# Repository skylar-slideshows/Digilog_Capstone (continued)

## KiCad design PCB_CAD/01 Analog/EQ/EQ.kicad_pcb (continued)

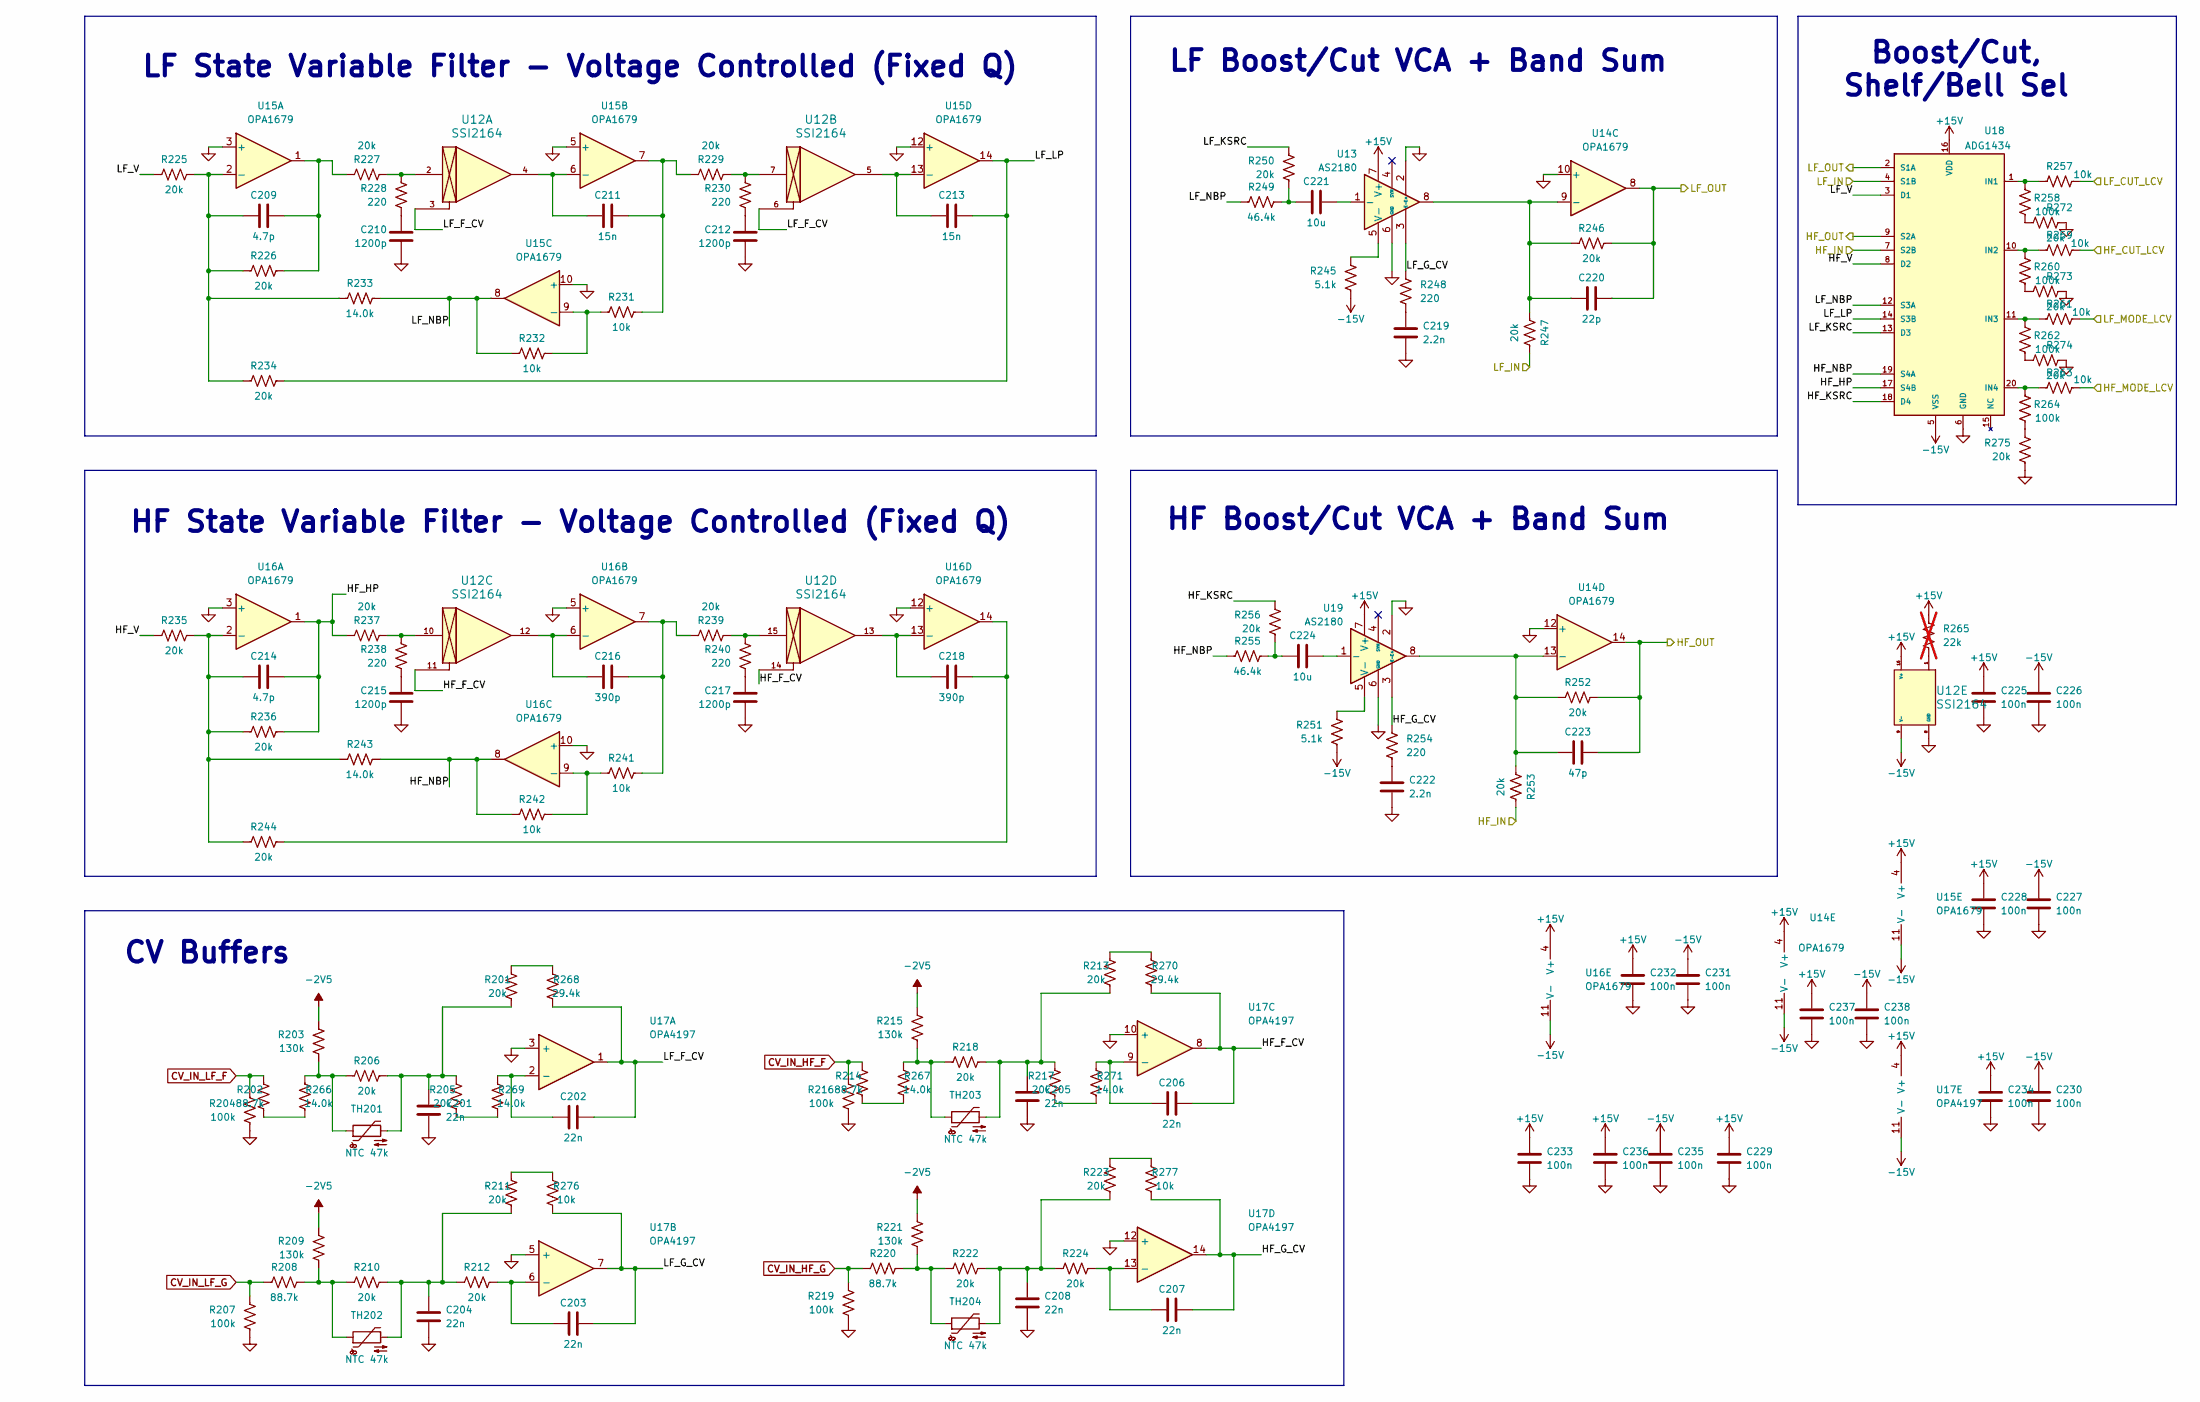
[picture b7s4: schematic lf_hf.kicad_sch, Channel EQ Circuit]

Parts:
C201, C202, C203, C204, C205, C206, C207, C208: 22n; C_1206_3216Metric; LCSC C7500389
C209, C214: 4.7p; C_0603_1608Metric; LCSC C282071
C210, C212, C215, C217: 1200p; C_1206_3216Metric; LCSC C527278
C211, C213: 15n; C_Rect_L7.2mm_W2.5mm_P5.00mm; LCSC dnp
C216, C218: 390p; C_0603_1608Metric; LCSC C107050
C219, C222: 2.2n; C_0805_2012Metric; LCSC C107103
C220: 22p; C_0603_1608Metric; LCSC C105620
C221, C224: 10u; CP_Elec_6.3x5.4_Nichicon; LCSC C340735
C223: 47p; C_0603_1608Metric; LCSC C105622
C225, C226, C227, C228, C229, C230, C231, C232, C233, C234, C235, C236, C237, C238: 100n; C_0603_1608Metric; LCSC C1591
R201, R205, R206, R210, R211, R212, R213, R217, R218, R222, R223, R224, R225, R226, R227, R229, R234, R235, R236, R237, R239, R244, R246, R247, R250, R252, R253, R256, R272, R273, R274, R275: 20k; R_0603_1608Metric; LCSC C311888
R202, R208, R214, R220: 88.7k; R_0603_1608Metric; LCSC C728599
R203, R209, R215, R221: 130k; R_0603_1608Metric; LCSC C473257
R204, R207, R216, R219, R258, R260, R262, R264: 100k; R_0603_1608Metric; LCSC C122538
R228, R230, R238, R240, R248, R254: 220; R_0603_1608Metric; LCSC C318124
R231, R232, R241, R242, R257, R259, R261, R263, R276, R277: 10k; R_0603_1608Metric; LCSC C95204
R233, R243, R266, R267, R269, R271: 14.0k; R_0603_1608Metric; LCSC C705941
R245, R251: 5.1k; R_0603_1608Metric; LCSC C122969
R249, R255: 46.4k; R_0603_1608Metric; LCSC C861420
R265: 22k; R_0603_1608Metric; LCSC C335085; not fitted
R268, R270: 29.4k; R_0603_1608Metric; LCSC C667085
TH201, TH202, TH203, TH204: NTC 47k; R_Axial_DIN0207_L6.3mm_D2.5mm_P2.54mm_Vertical; MPN NTCLE100E3473JB0; LCSC dnp
U12: SSI2164; SSI2164_breakout; LCSC dnp
U13, U19: AS2180; PinHeader_1x08_P2.54mm_Vertical; LCSC dnp
U14, U15, U16: OPA1679; SOIC-14_3.9x8.7mm_P1.27mm; LCSC C2878631
U17: OPA4197; SOIC-14_3.9x8.7mm_P1.27mm; LCSC C2058532
U18: ADG1434; TSSOP-20_4.4x6.5mm_P0.65mm; LCSC C408906

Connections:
+15V: C225.1, C228.1, C229.1, C232.1, C233.1, C234.1, C236.1, C237.1, R265.1, U12.16 (V+), U13.7 (V+), U14.4 (V+), U15.4 (V+), U16.4 (V+), U17.4 (V+), U18.16 (VDD), U19.7 (V+); also elsewhere on the board
-2V5: R203.1, R209.1, R215.1, R221.1; also elsewhere on the board
-15V: C226.1, C227.1, C230.1, C231.1, C235.1, C238.1, R245.2, R251.2, U12.9 (V-), U14.11 (V-), U15.11 (V-), U16.11 (V-), U17.11 (V-), U18.5 (VSS); also elsewhere on the board
/EQ_OUT: C223.2, R252.2, U14.14, U18.9 (S2A); also elsewhere on the board
/LF_HF/HF_CUT_LCV: R259.2; also elsewhere on the board
/LF_HF/HF_F_CV: C206.2, R270.2, U12.11, U12.14, U17.8
/LF_HF/HF_G_CV: C207.2, R254.1, R277.2, U17.14, U19.3 (E-)
/LF_HF/HF_HP: C214.2, R236.2, R237.1, U16.1, U18.17 (S4B)
/LF_HF/HF_KSRC: R256.1, U18.18 (D4)
/LF_HF/HF_MODE_LCV: R263.2; also elsewhere on the board
/LF_HF/HF_NBP: R242.1, R243.2, R255.1, U16.8, U18.19 (S4A)
/LF_HF/HF_V: R235.1, U18.8 (D2)
/LF_HF/LF_CUT_LCV: R257.2; also elsewhere on the board
/LF_HF/LF_F_CV: C202.2, R268.2, U12.3, U12.6, U17.1
/LF_HF/LF_G_CV: C203.2, R248.1, R276.2, U13.3 (E-), U17.7
/LF_HF/LF_IN: R247.2, U18.4 (S1B); also elsewhere on the board
/LF_HF/LF_KSRC: R250.1, U18.13 (D3)
/LF_HF/LF_LP: C213.2, R234.2, U15.14, U18.14 (S3B)
/LF_HF/LF_MODE_LCV: R261.2; also elsewhere on the board
/LF_HF/LF_NBP: R232.1, R233.2, R249.1, U15.8, U18.12 (S3A)
/LF_HF/LF_OUT: C220.2, R246.2, U14.8, U18.2 (S1A); also elsewhere on the board
/LF_HF/LF_V: R225.1, U18.3 (D1)
CV_IN_HF_F: R214.1, R216.1; also elsewhere on the board
CV_IN_HF_G: R219.1, R220.1; also elsewhere on the board
CV_IN_LF_F: R202.1, R204.1; also elsewhere on the board
CV_IN_LF_G: R207.1, R208.1; also elsewhere on the board
GND: C201.2, C204.2, C205.2, C208.2, C210.2, C212.2, C215.2, C217.2, C219.2, C222.2, C225.2, C226.2, C227.2, C228.2, C229.2, C230.2, C231.2, C232.2, C233.2, C234.2, C235.2, C236.2, C237.2, C238.2, R204.2, R207.2, R216.2, R219.2, R272.2, R273.2, R274.2, R275.2, U12.8 (GND), U13.2 (E+), U13.6 (GND), U14.10 (+), U14.12 (+), U15.3 (+), U15.5 (+), U15.10 (+), U15.12 (+), U16.3 (+), U16.5 (+), U16.10 (+), U16.12 (+), U17.3 (+), U17.5 (+), U17.10 (+), U17.12 (+), U18.6 (GND), U19.2 (E+), U19.6 (GND); also elsewhere on the board
HMF_OUT: R253.2, U18.7 (S2B); also elsewhere on the board
unnamed: C201.1, R201.1, R205.1, R206.2, TH201.2
unnamed: C204.1, R210.2, R211.1, R212.1, TH202.2
unnamed: C205.1, R213.1, R217.1, R218.2, TH203.2
unnamed: C208.1, R222.2, R223.1, R224.1, TH204.2
unnamed: C209.2, R226.2, R227.1, U15.1
unnamed: C210.1, R228.2
unnamed: C211.2, R229.1, R231.2, U15.7
unnamed: C212.1, R230.2
unnamed: C215.1, R238.2
unnamed: C216.2, R239.1, R241.2, U16.7
unnamed: C217.1, R240.2
unnamed: C218.2, R244.2, U16.14
unnamed: C219.1, R248.2
unnamed: C221.1, R249.2, R250.2
unnamed: C222.1, R254.2
unnamed: C224.1, R255.2, R256.2
unnamed: R201.2, R268.1
unnamed: R202.2, R266.1
unnamed: R203.2, R206.1, R266.2, TH201.1
unnamed: R205.2, R269.1
unnamed: R208.2, R209.2, R210.1, TH202.1
unnamed: R211.2, R276.1
unnamed: R213.2, R270.1
unnamed: R214.2, R267.1
unnamed: R215.2, R218.1, R267.2, TH203.1
unnamed: R217.2, R271.1
unnamed: R220.2, R221.2, R222.1, TH204.1
unnamed: R223.2, R277.1
unnamed: R227.2, R228.1, U12.2
unnamed: R229.2, R230.1, U12.7
unnamed: R237.2, R238.1, U12.10
unnamed: R239.2, R240.1, U12.15
unnamed: R258.2, R272.1
unnamed: R260.2, R273.1
unnamed: R262.2, R274.1
unnamed: R264.2, R275.1
unnamed: R265.2, U12.1
unnamed: C221.2, U13.1 (-)
unnamed: R245.1, U13.5 (V-)
unnamed: C220.1, R246.1, R247.1, U13.8, U14.9 (-)
unnamed: C223.1, R252.1, R253.1, U14.13 (-), U19.8
unnamed: C209.1, R225.2, R226.1, R233.1, R234.1, U15.2 (-)
unnamed: C211.1, U12.4, U15.6 (-)
unnamed: R231.1, R232.2, U15.9 (-)
unnamed: C213.1, U12.5, U15.13 (-)
unnamed: C214.1, R235.2, R236.1, R243.1, R244.1, U16.2 (-)
unnamed: C216.1, U12.12, U16.6 (-)
unnamed: R241.1, R242.2, U16.9 (-)
unnamed: C218.1, U12.13, U16.13 (-)
unnamed: C202.1, R269.2, U17.2 (-)
unnamed: C203.1, R212.2, U17.6 (-)
unnamed: C206.1, R271.2, U17.9 (-)
unnamed: C207.1, R224.2, U17.13 (-)
unnamed: R257.1, R258.1, U18.1 (IN1)
unnamed: R259.1, R260.1, U18.10 (IN2)
unnamed: R261.1, R262.1, U18.11 (IN3)
unnamed: R263.1, R264.1, U18.20 (IN4)
unnamed: C224.2, U19.1 (-)
unnamed: R251.1, U19.5 (V-)

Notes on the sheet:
LF Boost/Cut VCA + Band Sum
LF State Variable Filter - Voltage Controlled (Fixed Q)
HF Boost/Cut VCA + Band Sum
HF State Variable Filter - Voltage Controlled (Fixed Q)
Boost/Cut, Shelf/Bell Sel
CV Buffers

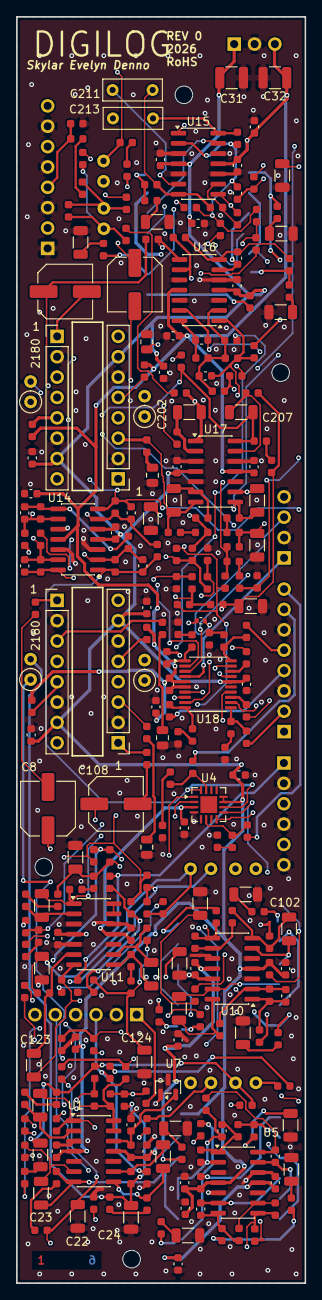
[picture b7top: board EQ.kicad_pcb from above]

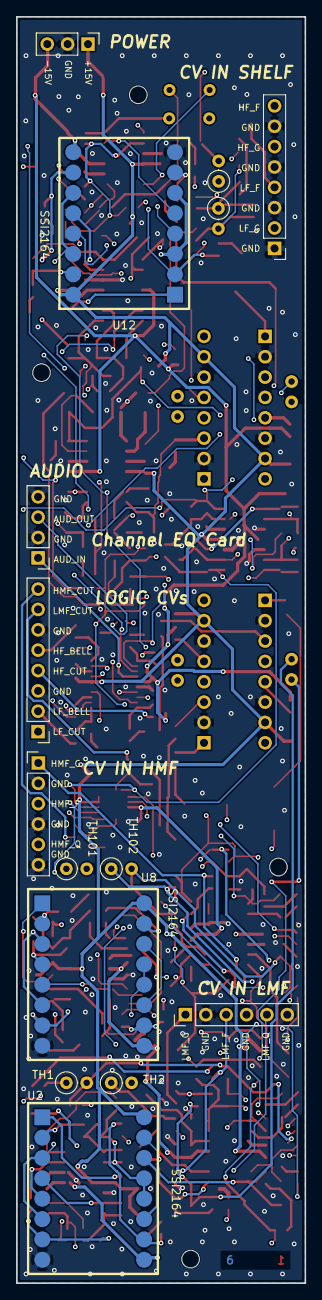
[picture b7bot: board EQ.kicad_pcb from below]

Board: 6 copper layers, 36.0 x 158.0 mm, 297 parts (15 on the bottom side), 185 nets.

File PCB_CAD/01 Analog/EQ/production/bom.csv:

Designator,Footprint,Quantity,Value,LCSC Part #
"C1, C101, C209, C214",0603,4,4.7p,C282071
"C10, C110, C219, C222",0805,4,2.2n,C107103
"C102, C103",1206,2,1.2n,C527278
"C104, C105, C106, C107, C210, C212, C215, C217, C4, C5, C6, C7",1206,12,1200p,C527278
"C108, C221, C224, C8",CP_Elec_6.3x5.4_Nichicon,4,10u,C340735
"C109, C220, C9",0603,3,22p,C105620
"C11, C111, C112, C113, C114, C117, C12, C127, C128, C13, C14, C17, C18, C19, C225, C226, C227, C228, C229, C230, C231, C232, C233, C234, C235, C236, C237, C238, C27, C28, C29",0603,31,100n,C1591
"C120, C121, C122, C123, C124, C125, C20, C201, C202, C203, C204, C205, C206, C207, C208, C21, C22, C23, C24, C25",1206,20,22n,C7500389
"C2, C3",0603,2,3.3n,C107048
"C211, C213",C_Rect_L7.2mm_W2.5mm_P5.00mm,2,15n,dnp
"C216, C218",0603,2,390p,C107050
C223,0603,1,47p,C105622
C26,0603,1,100n,C1590
"C31, C32",1210,2,22u 25V,C21397
J1,PinHeader_1x04_P2.54mm_Vertical,1,AUDIO,dnp
J2,PinHeader_1x08_P2.54mm_Vertical,1,LF_HF_CV,dnp
J3,PinHeader_1x08_P2.54mm_Vertical,1,LOGIC_CV,dnp
J4,PinHeader_1x03_P2.54mm_Vertical,1,POWER,dnp
J5,PinHeader_1x06_P2.54mm_Vertical,1,HMF_CV,dnp
J6,PinHeader_1x06_P2.54mm_Vertical,1,LMF_CV,dnp
"R1, R101, R103, R104, R105, R108, R116, R123, R124, R125, R129, R135, R136, R137, R139, R16, R201, R205, R206, R210, R211, R212, R213, R217, R218, R222, R223, R224, R225, R226, R227, R229, R23, R234, R235, R236, R237, R239, R24, R244, R246, R247, R25, R250, R252, R253, R256, R272, R273, R274, R275, R29, R3, R35, R36, R37, R39, R4, R47, R48, R5, R8",0603,62,20k,C311888
"R10, R109, R11, R110, R111, R112, R117, R12, R17, R228, R230, R238, R240, R248, R254, R9",0603,16,220,C318124
"R102, R106, R107, R113, R13, R146, R18, R2, R231, R232, R241, R242, R257, R259, R261, R263, R276, R277, R40, R50, R6, R7",0603,22,10k,C95204
"R114, R14, R245, R251",0603,4,5.1k,C122969
"R120, R126, R132, R19, R20, R204, R207, R216, R219, R258, R26, R260, R262, R264, R32, R41",0603,16,100k,C122538
"R121, R127, R133, R202, R208, R21, R214, R220, R27, R33",0603,10,88.7k,C728599
"R122, R128, R134, R203, R209, R215, R22, R221, R28, R34",0603,10,130k,C473257
"R130, R131, R143, R268, R270, R30, R31, R45",0603,8,29.4k,C667085
"R140, R265, R42",0603,3,22k,C335085
"R141, R142, R144, R145, R233, R243, R266, R267, R269, R271, R43, R44, R46, R49",0603,14,14.0k,C705941
R15,0402,1,100,C317909
"R249, R255, R38",0603,3,46.4k,C861420
"TH1, TH101, TH102, TH103, TH2, TH201, TH202, TH203, TH204, TH3",R_Axial_DIN0207_L6.3mm_D2.5mm_P2.54mm_Vertical,10,NTC 47k,dnp
"U1, U11, U17",SOIC-14_3.9x8.7mm_P1.27mm,3,OPA4197,C2058532
"U10, U14, U15, U16, U5",SOIC-14_3.9x8.7mm_P1.27mm,5,OPA1679,C2057264
"U12, U2, U8",SSI2164_breakout,3,SSI2164,dnp
"U13, U19, U3, U9",PinHeader_1x08_P2.54mm_Vertical,4,AS2180,dnp
U18,TSSOP-20_4.4x6.5mm_P0.65mm,1,ADG1434,C408906
U4,Analog_LFCSP-16-1EP_4x4mm_P0.65mm_EP2.1x2.1mm,1,ADG1436,C655227
U7,SOT-23,1,ADR5041,C659596

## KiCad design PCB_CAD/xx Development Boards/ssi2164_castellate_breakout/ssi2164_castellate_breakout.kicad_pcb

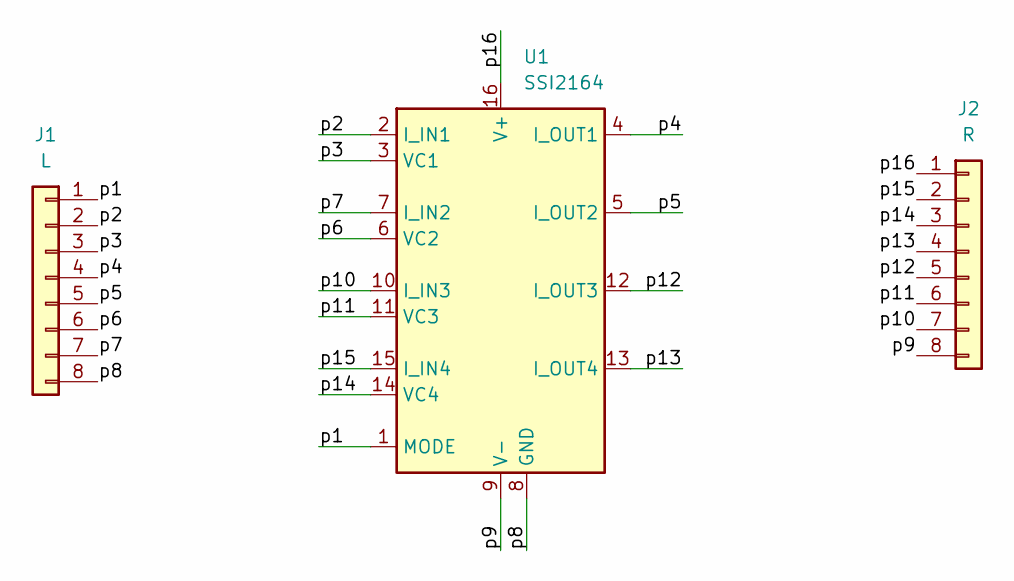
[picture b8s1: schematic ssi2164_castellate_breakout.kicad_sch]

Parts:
J1: L; PinHeader_1x08_P2.54mm_Vertical_big
J2: R; PinHeader_1x08_P2.54mm_Vertical_big
U1: SSI2164; SOIC-16_3.9x9.9mm_P1.27mm

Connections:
/p1: J1.1, U1.1 (MODE)
/p2: J1.2, U1.2 (I_IN1)
/p3: J1.3, U1.3 (VC1)
/p4: J1.4, U1.4 (I_OUT1)
/p5: J1.5, U1.5 (I_OUT2)
/p6: J1.6, U1.6 (VC2)
/p7: J1.7, U1.7 (I_IN2)
/p8: J1.8, U1.8 (GND)
/p9: J2.8, U1.9 (V-)
/p10: J2.7, U1.10 (I_IN3)
/p11: J2.6, U1.11 (VC3)
/p12: J2.5, U1.12 (I_OUT3)
/p13: J2.4, U1.13 (I_OUT4)
/p14: J2.3, U1.14 (VC4)
/p15: J2.2, U1.15 (I_IN4)
/p16: J2.1, U1.16 (V+)

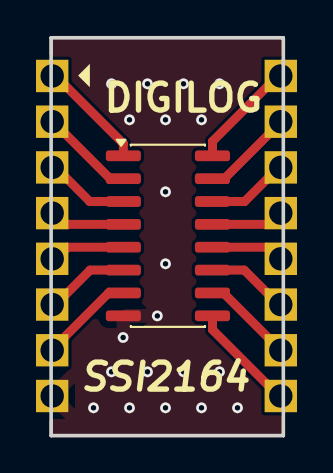
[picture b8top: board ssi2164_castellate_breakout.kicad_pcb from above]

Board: 2 copper layers, 12.9 x 22.1 mm, 3 parts (0 on the bottom side), 16 nets.

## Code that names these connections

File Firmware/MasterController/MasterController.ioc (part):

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Mcu.Name=STM32G474V(B-C-E)Tx
Mcu.Package=LQFP100
Mcu.UserName=STM32G474VETx
PA0.GPIOParameters=GPIO_Label
PA0.GPIO_Label=SCRUB_A
PA0.Signal=S_TIM2_CH1
PA1.GPIOParameters=GPIO_Label
PA1.GPIO_Label=SCRUB_B
PA1.Signal=S_TIM2_CH2
PA10.GPIOParameters=GPIO_Label
PA10.GPIO_Label=LDAC
PA10.Signal=GPIO_Output
PA11.Mode=Device
PA11.Signal=USB_DM
PA12.Mode=Device
PA12.Signal=USB_DP
PA13.GPIOParameters=GPIO_Label
PA13.GPIO_Label=SWD_SWDIO
PA13.Mode=Serial_Wire
PA13.Signal=SYS_JTMS-SWDIO
PA14.GPIOParameters=GPIO_Label
PA14.GPIO_Label=SWD_SWCLK
PA14.Mode=Serial_Wire
PA14.Signal=SYS_JTCK-SWCLK
PA15.GPIOParameters=PinState,GPIO_Label
PA15.GPIO_Label=DISK_CS
PA15.PinState=GPIO_PIN_SET
PA15.Signal=GPIO_Output
PA2.Mode=Asynchronous
PA2.Signal=USART2_TX
PA3.Mode=Asynchronous
PA3.Signal=USART2_RX
PA5.GPIOParameters=GPIO_Label
PA5.GPIO_Label=__MASTER_Clock
PA5.Mode=Full_Duplex_Master
PA5.Signal=SPI1_SCK
PA6.GPIOParameters=GPIO_Label
PA6.GPIO_Label=__MASTER_MISO
PA6.Mode=Full_Duplex_Master
PA6.Signal=SPI1_MISO
PA7.GPIOParameters=GPIO_Label
PA7.GPIO_Label=__MASTER_MOSI
PA7.Mode=Full_Duplex_Master
PA7.Signal=SPI1_MOSI
PA8.Mode=I2C
PA8.Signal=I2C2_SDA
PA9.GPIOParameters=GPIO_Label
PA9.GPIO_Label=I2C2_Clock
PA9.Mode=I2C
PA9.Signal=I2C2_SCL
PB10.GPIOParameters=GPIO_Label
PB10.GPIO_Label=DISP_INT
PB10.Signal=GPXTI10
PB13.GPIOParameters=GPIO_Label
PB13.GPIO_Label=LED_CLK
PB13.Mode=TX_Only_Simplex_Unidirect_Master
PB13.Signal=SPI2_SCK
PB14.GPIOParameters=GPIO_Label
PB14.GPIO_Label=LED_LAT
PB14.Signal=GPIO_Output
PB15.GPIOParameters=GPIO_Label
PB15.GPIO_Label=LED_DATA
PB15.Mode=TX_Only_Simplex_Unidirect_Master
PB15.Signal=SPI2_MOSI
PB3.GPIOParameters=PinState,GPIO_Label
PB3.GPIO_Label=CS_Bucket7
PB3.PinState=GPIO_PIN_SET
PB3.Signal=GPIO_Output
PB4.GPIOParameters=PinState,GPIO_Label
PB4.GPIO_Label=CS_Bucket6
PB4.PinState=GPIO_PIN_SET
PB4.Signal=GPIO_Output
PB5.GPIOParameters=PinState,GPIO_Label
PB5.GPIO_Label=CS_Bucket5
PB5.PinState=GPIO_PIN_SET
PB5.Signal=GPIO_Output
PB6.GPIOParameters=PinState,GPIO_Label
PB6.GPIO_Label=CS_Bucket4
PB6.PinState=GPIO_PIN_SET
PB6.Signal=GPIO_Output
PB7.GPIOParameters=PinState,GPIO_Label
PB7.GPIO_Label=CS_Bucket3
PB7.PinState=GPIO_PIN_SET
PB7.Signal=GPIO_Output
PB9.GPIOParameters=PinState,GPIO_Label
PB9.GPIO_Label=CS_Bucket2
PB9.PinState=GPIO_PIN_SET
PB9.Signal=GPIO_Output
PC1.GPIOParameters=GPIO_Label
PC1.GPIO_Label=LED_PWM
PC1.Signal=S_TIM1_CH2
PC10.GPIOParameters=GPIO_Label
PC10.GPIO_Label=DISK_SCK
PC10.Mode=Full_Duplex_Master
PC10.Signal=SPI3_SCK
PC11.GPIOParameters=GPIO_Label
PC11.GPIO_Label=DISK_MISO
PC11.Mode=Full_Duplex_Master
PC11.Signal=SPI3_MISO
PC12.GPIOParameters=GPIO_Label
PC12.GPIO_Label=DISK_MOSI
PC12.Mode=Full_Duplex_Master
PC12.Signal=SPI3_MOSI
PC2.GPIOParameters=GPIO_Label
PC2.GPIO_Label=Disp_PWM
PC2.Signal=S_TIM1_CH3
PD0.Mode=16b-d1
PD0.Signal=FMC_D2
PD1.Mode=16b-d1
PD1.Signal=FMC_D3
PD10.Mode=16b-d1
PD10.Signal=FMC_D15
PD14.Mode=16b-d1
PD14.Signal=FMC_D0
PD15.Mode=16b-d1
PD15.Signal=FMC_D1
PD3.GPIOParameters=GPIO_PuPd,GPIO_Label,GPIO_ModeDefaultOutputPP
PD3.GPIO_Label=DISP_RESET
PD3.GPIO_ModeDefaultOutputPP=GPIO_MODE_OUTPUT_OD
PD3.GPIO_PuPd=GPIO_NOPULL
PD3.Signal=GPIO_Output
PD4.Mode=Lcd1
PD4.Signal=FMC_NOE
PD5.Mode=Lcd1
PD5.Signal=FMC_NWE
PD6.Signal=FMC_NWAIT
PD7.Mode=NorPsramChipSelect1_1
PD7.Signal=FMC_NE1
PD8.Mode=16b-d1
PD8.Signal=FMC_D13
PD9.Mode=16b-d1
PD9.Signal=FMC_D14
PE0.GPIOParameters=PinState,GPIO_Label
PE0.GPIO_Label=CS_Bucket1
PE0.PinState=GPIO_PIN_SET
PE0.Signal=GPIO_Output
PE1.GPIOParameters=PinState,GPIO_Label
PE1.GPIO_Label=CS_Bucket0
PE1.PinState=GPIO_PIN_SET
PE1.Signal=GPIO_Output
PE10.Mode=16b-d1
PE10.Signal=FMC_D7
PE11.Mode=16b-d1
PE11.Signal=FMC_D8
PE12.Mode=16b-d1
PE12.Signal=FMC_D9
PE13.Mode=16b-d1
PE13.Signal=FMC_D10
PE14.Mode=16b-d1
PE14.Signal=FMC_D11
PE15.Mode=16b-d1
PE15.Signal=FMC_D12
PE2.GPIOParameters=GPIO_Label
PE2.GPIO_Label=LCV_AUX1
PE2.Signal=GPIO_Output
PE3.GPIOParameters=GPIO_Label
PE3.GPIO_Label=LCV_AUX2
PE3.Signal=GPIO_Output
PE4.GPIOParameters=GPIO_Label
PE4.GPIO_Label=LCV_AUX3
PE4.Signal=GPIO_Output
PE5.GPIOParameters=GPIO_Label
PE5.GPIO_Label=LCV_AUX4
PE5.Signal=GPIO_Output
PE7.Mode=16b-d1
PE7.Signal=FMC_D4
PE8.Mode=16b-d1
PE8.Signal=FMC_D5
PE9.Mode=16b-d1
PE9.Signal=FMC_D6
PF0-OSC_IN.GPIOParameters=GPIO_Label
PF0-OSC_IN.GPIO_Label=_OSC_IN
PF0-OSC_IN.Mode=HSE-External-Oscillator
PF0-OSC_IN.Signal=RCC_OSC_IN
PF1-OSC_OUT.GPIOParameters=GPIO_Label
PF1-OSC_OUT.GPIO_Label=_OSC_OUT
PF1-OSC_OUT.Mode=HSE-External-Oscillator
PF1-OSC_OUT.Signal=RCC_OSC_OUT
PF10.Mode=A0_1
PF10.Signal=FMC_A0
PF2.GPIOParameters=GPIO_Label
PF2.GPIO_Label=LED_TEST
PF2.Signal=GPIO_Output
RCC.HSE_VALUE=24000000
RCC.SYSCLKFreq_VALUE=170000000
RCC.SYSCLKSource=RCC_SYSCLKSOURCE_PLLCLK
board=custom

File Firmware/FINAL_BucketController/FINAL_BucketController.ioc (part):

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Mcu.Name=STM32G474V(B-C-E)Tx
Mcu.Package=LQFP100
Mcu.UserName=STM32G474VETx
PA0.GPIOParameters=GPIO_Label
PA0.GPIO_Label=SHIFTREG_Latch
PA0.Signal=GPIO_Output
PA1.GPIOParameters=GPIO_Label
PA1.GPIO_Label=F0_MoB
PA1.Signal=S_TIM2_CH2
PA10.GPIOParameters=GPIO_Label
PA10.GPIO_Label=F1_MoB
PA10.Signal=S_TIM2_CH4
PA11.GPIOParameters=GPIO_Label
PA11.GPIO_Label=SHIFTREG_Clock
PA11.Signal=GPIO_Output
PA12.GPIOParameters=GPIO_Label
PA12.GPIO_Label=SHIFTREG_Data
PA12.Signal=GPIO_Output
PA13.GPIOParameters=GPIO_Label
PA13.GPIO_Label=__SWDIO
PA13.Mode=Serial_Wire
PA13.Signal=SYS_JTMS-SWDIO
PA14.GPIOParameters=GPIO_Label
PA14.GPIO_Label=__SWCLK
PA14.Mode=Serial_Wire
PA14.Signal=SYS_JTCK-SWCLK
PA15.GPIOParameters=GPIO_Label
PA15.GPIO_Label=I2C1_Clock
PA15.Mode=I2C
PA15.Signal=I2C1_SCL
PA2.GPIOParameters=GPIO_Label
PA2.GPIO_Label=__USART2_TX
PA2.Mode=Asynchronous
PA2.Signal=USART2_TX
PA3.GPIOParameters=GPIO_Label
PA3.GPIO_Label=__USART2_RX
PA3.Mode=Asynchronous
PA3.Signal=USART2_RX
PA4.GPIOParameters=GPIO_Label
PA4.GPIO_Label=F2_MoB
PA4.Signal=S_TIM3_CH2
PA5.GPIOParameters=GPIO_Label
PA5.GPIO_Label=F0_MoA
PA5.Signal=S_TIM2_CH1
PA6.GPIOParameters=GPIO_Label
PA6.GPIO_Label=F2_MoA
PA6.Signal=S_TIM3_CH1
PA7.GPIOParameters=GPIO_Label
PA7.GPIO_Label=MASTER_MOSI
PA7.Mode=Full_Duplex_Slave
PA7.Signal=SPI1_MOSI
PA8.GPIOParameters=GPIO_Label
PA8.GPIO_Label=I2C2_Data
PA8.Mode=I2C
PA8.Signal=I2C2_SDA
PA9.GPIOParameters=GPIO_Label
PA9.GPIO_Label=I2C2_Clock
PA9.Mode=I2C
PA9.Signal=I2C2_SCL
PB0.GPIOParameters=GPIO_Label
PB0.GPIO_Label=F3_MoA
PB0.Signal=S_TIM3_CH3
PB1.GPIOParameters=GPIO_Label
PB1.GPIO_Label=COMP_ADC1
PB1.Mode=IN12-Single-Ended
PB1.Signal=ADC1_IN12
PB10.GPIOParameters=GPIO_Label
PB10.GPIO_Label=F1_MoA
PB10.Signal=S_TIM2_CH3
PB11.GPIOParameters=GPIO_Label
PB11.GPIO_Label=LED_Data
PB11.Signal=GPIO_Output
PB12.GPIOParameters=GPIO_Label
PB12.GPIO_Label=LED_Clock
PB12.Signal=GPIO_Output
PB13.GPIOParameters=GPIO_Label
PB13.GPIO_Label=COMP_CV1
PB13.Mode=Follower_Internally_Connected
PB13.Signal=OPAMP3_VINP
PB14.GPIOParameters=GPIO_Label
PB14.GPIO_Label=LED_Latch
PB14.Signal=GPIO_Output
PB15.GPIOParameters=GPIO_Label
PB15.GPIO_Label=DISP_CS3
PB15.Signal=GPIO_Output
PB2.GPIOParameters=GPIO_Label
PB2.GPIO_Label=DISP_CS0
PB2.Signal=GPIO_Output
PB3.GPIOParameters=GPIO_Label
PB3.GPIO_Label=MASTER_Clock
PB3.Mode=Full_Duplex_Slave
PB3.Signal=SPI1_SCK
PB4.GPIOParameters=GPIO_Label
PB4.GPIO_Label=MASTER_MISO
PB4.Mode=Full_Duplex_Slave
PB4.Signal=SPI1_MISO
PB5.GPIOParameters=GPIO_Label
PB5.GPIO_Label=I2C3_Data
PB5.Mode=I2C
PB5.Signal=I2C3_SDA
PB6.GPIOParameters=GPIO_Label
PB6.GPIO_Label=DAC_LDAC2
PB6.Signal=GPIO_Output
PB9.GPIOParameters=GPIO_Label
PB9.GPIO_Label=I2C1_Data
PB9.Mode=I2C
PB9.Signal=I2C1_SDA
PC0.GPIOParameters=GPIO_Label
PC0.GPIO_Label=MASTER_CS_IN
PC0.Signal=GPIO_Input
PC1.GPIOParameters=GPIO_Label
PC1.GPIO_Label=LED_PWM
PC1.Signal=S_TIM1_CH2
PC10.GPIOParameters=GPIO_Label
PC10.GPIO_Label=F3_Touch
PC10.Signal=GPIO_Input
PC11.GPIOParameters=GPIO_Label
PC11.GPIO_Label=F2_Touch
PC11.Signal=GPIO_Input
PC12.GPIOParameters=GPIO_Label
PC12.GPIO_Label=F1_Touch
PC12.Signal=GPIO_Input
PC2.GPIOParameters=GPIO_Label
PC2.GPIO_Label=DISP_PWM
PC2.Signal=S_TIM1_CH3
PC3.GPIOParameters=GPIO_Label
PC3.GPIO_Label=COMP_ADC0
PC3.Mode=IN9-Single-Ended
PC3.Signal=ADC1_IN9
PC4.GPIOParameters=GPIO_Label
PC4.GPIO_Label=COMP_ADC2
PC4.Mode=IN5-Single-Ended
PC4.Signal=ADC2_IN5
PC5.GPIOParameters=GPIO_Label
PC5.GPIO_Label=COMP_ADC3
PC5.Mode=IN11-Single-Ended
PC5.Signal=ADC2_IN11
PC6.GPIOParameters=GPIO_Label
PC6.GPIO_Label=I2C4_Clock
PC6.Mode=I2C
PC6.Signal=I2C4_SCL
PC7.GPIOParameters=GPIO_Label
PC7.GPIO_Label=I2C4_Data
PC7.Mode=I2C
PC7.Signal=I2C4_SDA
PC8.GPIOParameters=GPIO_Label
PC8.GPIO_Label=I2C3_Clock
PC8.Mode=I2C
PC8.Signal=I2C3_SCL
PD0.GPIOParameters=GPIO_Label
PD0.GPIO_Label=DISP_D2_FMC
PD0.Mode=8b-d1
PD0.Signal=FMC_D2
PD1.GPIOParameters=GPIO_Label
PD1.GPIO_Label=DISP_D3_FMC
PD1.Mode=8b-d1
PD1.Signal=FMC_D3
PD10.GPIOParameters=GPIO_Label
PD10.GPIO_Label=F1_ADC
PD10.Mode=IN7-Single-Ended
PD10.Signal=ADC3_IN7
PD11.GPIOParameters=GPIO_Label
PD11.GPIO_Label=COMP_CV2
PD11.Mode=Follower_Internally_Connected
PD11.Signal=OPAMP4_VINP
PD12.GPIOParameters=GPIO_Label
PD12.GPIO_Label=COMP_CV3
PD12.Mode=Follower_Internally_Connected
PD12.Signal=OPAMP5_VINP
PD13.GPIOParameters=GPIO_Label
PD13.GPIO_Label=F2_ADC
PD13.Mode=IN10-Single-Ended
PD13.Signal=ADC3_IN10
PD14.GPIOParameters=GPIO_Label
PD14.GPIO_Label=DISP_D0_FMC
PD14.Mode=8b-d1
PD14.Signal=FMC_D0
PD15.GPIOParameters=GPIO_Label
PD15.GPIO_Label=DISP_D1_FMC
PD15.Mode=8b-d1
PD15.Signal=FMC_D1
PD2.GPIOParameters=GPIO_Label
PD2.GPIO_Label=F0_Touch
PD2.Signal=GPIO_Input
PD3.GPIOParameters=GPIO_Label
PD3.GPIO_Label=DAC_LDAC4
PD3.Signal=GPIO_Output
PD4.GPIOParameters=GPIO_Label
PD4.GPIO_Label=DISP_NOE_FMC
PD4.Mode=Lcd1
PD4.Signal=FMC_NOE
PD5.GPIOParameters=GPIO_Label
PD5.GPIO_Label=DISP_NWE_FMC
PD5.Mode=Lcd1
PD5.Signal=FMC_NWE
PD6.GPIOParameters=GPIO_Label
PD6.GPIO_Label=DAC_LDAC3
PD6.Signal=GPIO_Output
PD7.GPIOParameters=GPIO_Label
PD7.GPIO_Label=DISP_NE1_FMC
PD7.Mode=NorPsramChipSelect1_1
PD7.Signal=FMC_NE1
PD9.GPIOParameters=GPIO_Label
PD9.GPIO_Label=COMP_CV0
PD9.Mode=Follower_Internally_Connected
PD9.Signal=OPAMP6_VINP
PE0.GPIOParameters=GPIO_Label
PE0.GPIO_Label=DAC_LDAC1
PE0.Signal=GPIO_Output
PE1.GPIOParameters=GPIO_Label
PE1.GPIO_Label=DAC_LDAC0
PE1.Signal=GPIO_Output
PE10.GPIOParameters=GPIO_Label
PE10.GPIO_Label=DISP_D7_FMC
PE10.Mode=8b-d1
PE10.Signal=FMC_D7
PE11.GPIOParameters=GPIO_Label
PE11.GPIO_Label=F3_ADC
PE11.Mode=IN15-Single-Ended
PE11.Signal=ADC3_IN15
PE13.GPIOParameters=GPIO_Label
PE13.GPIO_Label=F0_ADC
PE13.Mode=IN3-Single-Ended
PE13.Signal=ADC3_IN3
PE14.GPIOParameters=GPIO_Label
PE14.GPIO_Label=DISP_CS1
PE14.Signal=GPIO_Output
PE15.GPIOParameters=GPIO_Label
PE15.GPIO_Label=DISP_CS2
PE15.Signal=GPIO_Output
PE4.GPIOParameters=GPIO_Label
PE4.GPIO_Label=DISP_RST
PE4.Signal=GPIO_Output
PE5.GPIOParameters=GPIO_Label
PE5.GPIO_Label=F3_MoB
PE5.Signal=S_TIM3_CH4
PE7.GPIOParameters=GPIO_Label
PE7.GPIO_Label=DISP_D4_FMC
PE7.Mode=8b-d1
PE7.Signal=FMC_D4
PE8.GPIOParameters=GPIO_Label
PE8.GPIO_Label=DISP_D5_FMC
PE8.Mode=8b-d1
PE8.Signal=FMC_D5
PE9.GPIOParameters=GPIO_Label
PE9.GPIO_Label=DISP_D6_FMC
PE9.Mode=8b-d1
PE9.Signal=FMC_D6
PF0-OSC_IN.GPIOParameters=GPIO_Label
PF0-OSC_IN.GPIO_Label=__OSC_IN
PF0-OSC_IN.Mode=HSE-External-Oscillator
PF0-OSC_IN.Signal=RCC_OSC_IN
PF1-OSC_OUT.GPIOParameters=GPIO_Label
PF1-OSC_OUT.GPIO_Label=__OSC_OUT
PF1-OSC_OUT.Mode=HSE-External-Oscillator
PF1-OSC_OUT.Signal=RCC_OSC_OUT
PF10.GPIOParameters=GPIO_Label
PF10.GPIO_Label=DISP_A0_FMC
PF10.Mode=A0_1
PF10.Signal=FMC_A0
PF2.GPIOParameters=GPIO_Label
PF2.GPIO_Label=LED_TEST
PF2.Signal=GPIO_Output
RCC.HSE_VALUE=24000000
RCC.SYSCLKFreq_VALUE=16000000
board=custom

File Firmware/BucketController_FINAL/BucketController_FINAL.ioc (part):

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Mcu.Name=STM32G474V(B-C-E)Tx
Mcu.Package=LQFP100
Mcu.UserName=STM32G474VETx
PA1.GPIOParameters=GPIO_Speed,GPIO_Label
PA1.GPIO_Label=F3_MB
PA1.GPIO_Speed=GPIO_SPEED_FREQ_HIGH
PA1.Signal=S_TIM2_CH2
PA10.GPIOParameters=GPIO_Label
PA10.GPIO_Label=DISP_PWM
PA10.Signal=S_TIM1_CH3
PA11.GPIOParameters=GPIO_Label
PA11.GPIO_Label=SHIFTREG_Clock
PA11.Signal=GPIO_Output
PA12.GPIOParameters=GPIO_Label
PA12.GPIO_Label=SHIFTREG_Data
PA12.Signal=GPIO_Output
PA13.GPIOParameters=GPIO_Label
PA13.GPIO_Label=__SWDIO
PA13.Mode=Serial_Wire
PA13.Signal=SYS_JTMS-SWDIO
PA14.GPIOParameters=GPIO_Label
PA14.GPIO_Label=__SWCLK
PA14.Mode=Serial_Wire
PA14.Signal=SYS_JTCK-SWCLK
PA15.GPIOParameters=GPIO_Label
PA15.GPIO_Label=I2C1_Clock
PA15.Mode=I2C
PA15.Signal=I2C1_SCL
PA2.GPIOParameters=GPIO_Label
PA2.GPIO_Label=__USART2_TX
PA2.Mode=Asynchronous
PA2.Signal=USART2_TX
PA3.GPIOParameters=GPIO_Label
PA3.GPIO_Label=__USART2_RX
PA3.Mode=Asynchronous
PA3.Signal=USART2_RX
PA4.GPIOParameters=GPIO_Label
PA4.GPIO_Label=COMP_CV3
PA4.Signal=COMP_DAC11_group
PA5.GPIOParameters=GPIO_Speed,GPIO_Label
PA5.GPIO_Label=F0_MA
PA5.GPIO_Speed=GPIO_SPEED_FREQ_HIGH
PA5.Signal=S_TIM2_CH1
PA6.GPIOParameters=GPIO_Speed,GPIO_Label
PA6.GPIO_Label=F1_MA
PA6.GPIO_Speed=GPIO_SPEED_FREQ_HIGH
PA6.Signal=S_TIM3_CH1
PA7.GPIOParameters=GPIO_Speed,GPIO_Label
PA7.GPIO_Label=F1_MB
PA7.GPIO_Speed=GPIO_SPEED_FREQ_HIGH
PA7.Signal=S_TIM3_CH2
PA8.GPIOParameters=GPIO_Label
PA8.GPIO_Label=I2C2_Data
PA8.Mode=I2C
PA8.Signal=I2C2_SDA
PA9.GPIOParameters=GPIO_Label
PA9.GPIO_Label=I2C2_Clock
PA9.Mode=I2C
PA9.Signal=I2C2_SCL
PB1.GPIOParameters=GPIO_Label
PB1.GPIO_Label=COMP_CV1
PB1.Mode=Follower-DAC_OUT2-INP
PB1.Signal=OPAMP3_VOUT
PB10.GPIOParameters=GPIO_Speed,GPIO_Label
PB10.GPIO_Label=F0_MB
PB10.GPIO_Speed=GPIO_SPEED_FREQ_HIGH
PB10.Signal=S_TIM2_CH3
PB11.GPIOParameters=GPIO_Label
PB11.GPIO_Label=COMP_CV0
PB11.Mode=Follower-DAC_OUT2-INP
PB11.Signal=OPAMP6_VOUT
PB12.GPIOParameters=GPIO_Label
PB12.GPIO_Label=COMP_CV2
PB12.Mode=Follower-DAC_OUT2-INP
PB12.Signal=OPAMP4_VOUT
PB13.GPIOParameters=GPIO_Speed,GPIO_Label
PB13.GPIO_Label=LED_Clock
PB13.GPIO_Speed=GPIO_SPEED_FREQ_LOW
PB13.Mode=TX_Only_Simplex_Unidirect_Master
PB13.Signal=SPI2_SCK
PB14.GPIOParameters=GPIO_Label
PB14.GPIO_Label=LED_Latch
PB14.Signal=GPIO_Output
PB15.GPIOParameters=GPIO_Speed,GPIO_Label
PB15.GPIO_Label=LED_Data
PB15.GPIO_Speed=GPIO_SPEED_FREQ_LOW
PB15.Mode=TX_Only_Simplex_Unidirect_Master
PB15.Signal=SPI2_MOSI
PB2.GPIOParameters=GPIO_Label
PB2.GPIO_Label=F1_TOUCH
PB2.Signal=GPIO_Input
PB3.GPIOParameters=GPIO_Label
PB3.GPIO_Label=SPI1_Clock
PB3.Mode=Full_Duplex_Slave
PB3.Signal=SPI1_SCK
PB4.GPIOParameters=GPIO_Label
PB4.GPIO_Label=SPI1_MISO
PB4.Mode=Full_Duplex_Slave
PB4.Signal=SPI1_MISO
PB5.GPIOParameters=GPIO_Label
PB5.GPIO_Label=SPI1_MOSI
PB5.Mode=Full_Duplex_Slave
PB5.Signal=SPI1_MOSI
PB6.GPIOParameters=GPIO_Label
PB6.GPIO_Label=SPI1_CS_IN
PB6.Signal=GPIO_Input
PB7.GPIOParameters=GPIO_Speed,GPIO_Label
PB7.GPIO_Label=F2_MA
PB7.GPIO_Speed=GPIO_SPEED_FREQ_HIGH
PB7.Signal=S_TIM3_CH4
PB9.GPIOParameters=GPIO_Label
PB9.GPIO_Label=I2C1_Data
PB9.Mode=I2C
PB9.Signal=I2C1_SDA
PC0.GPIOParameters=GPIO_Label
PC0.GPIO_Label=F3_ADC
PC0.Mode=IN6-Single-Ended
PC0.Signal=ADC2_IN6
PC1.GPIOParameters=GPIO_Label
PC1.GPIO_Label=LED_PWM
PC1.Signal=S_TIM1_CH2
PC10.GPIOParameters=GPIO_Label
PC10.GPIO_Label=LDAC4
PC10.Signal=GPIO_Output
PC11.GPIOParameters=GPIO_Label
PC11.GPIO_Label=LDAC3
PC11.Signal=GPIO_Output
PC12.GPIOParameters=GPIO_Label
PC12.GPIO_Label=LDAC2
PC12.Signal=GPIO_Output
PC13.GPIOParameters=GPIO_Label
PC13.GPIO_Label=DISP_RST
PC13.Signal=GPIO_Output
PC3.GPIOParameters=GPIO_Label
PC3.GPIO_Label=F2_ADC
PC3.Mode=IN9-Single-Ended
PC3.Signal=ADC2_IN9
PC5.GPIOParameters=GPIO_Label
PC5.GPIO_Label=SHIFTREG_LAT
PC5.Signal=GPIO_Output
PC6.GPIOParameters=GPIO_Label
PC6.GPIO_Label=I2C4_Clock
PC6.Mode=I2C
PC6.Signal=I2C4_SCL
PC7.GPIOParameters=GPIO_Label
PC7.GPIO_Label=I2C4_Data
PC7.Mode=I2C
PC7.Signal=I2C4_SDA
PC8.GPIOParameters=GPIO_Label
PC8.GPIO_Label=I2C3_Clock
PC8.Mode=I2C
PC8.Signal=I2C3_SCL
PC9.GPIOParameters=GPIO_Label
PC9.GPIO_Label=I2C3_Data
PC9.Mode=I2C
PC9.Signal=I2C3_SDA
PD0.GPIOParameters=GPIO_Label
PD0.GPIO_Label=DISP_D2_FMC
PD0.Mode=8b-d1
PD0.Signal=FMC_D2
PD1.GPIOParameters=GPIO_Label
PD1.GPIO_Label=DISP_D3_FMC
PD1.Mode=8b-d1
PD1.Signal=FMC_D3
PD10.GPIOParameters=GPIO_Label
PD10.GPIO_Label=COMP_ADC0
PD10.Mode=IN7-Single-Ended
PD10.Signal=ADC4_IN7
PD11.GPIOParameters=GPIO_Label
PD11.GPIO_Label=COMP_ADC1
PD11.Mode=IN8-Single-Ended
PD11.Signal=ADC4_IN8
PD12.GPIOParameters=GPIO_Label
PD12.GPIO_Label=COMP_ADC2
PD12.Mode=IN9-Single-Ended
PD12.Signal=ADC4_IN9
PD13.GPIOParameters=GPIO_Label
PD13.GPIO_Label=COMP_ADC3
PD13.Mode=IN10-Single-Ended
PD13.Signal=ADC4_IN10
PD14.GPIOParameters=GPIO_Label
PD14.GPIO_Label=DISP_D0_FMC
PD14.Mode=8b-d1
PD14.Signal=FMC_D0
PD15.GPIOParameters=GPIO_Label
PD15.GPIO_Label=DISP_D1_FMC
PD15.Mode=8b-d1
PD15.Signal=FMC_D1
PD2.GPIOParameters=GPIO_Label
PD2.GPIO_Label=LDAC0
PD2.Signal=GPIO_Output
PD3.GPIOParameters=GPIO_Label
PD3.GPIO_Label=LDAC1
PD3.Signal=GPIO_Output
PD4.GPIOParameters=GPIO_Label
PD4.GPIO_Label=DISP_NOE_FMC
PD4.Mode=Lcd1
PD4.Signal=FMC_NOE
PD5.GPIOParameters=GPIO_Label
PD5.GPIO_Label=DISP_NWE_FMC
PD5.Mode=Lcd1
PD5.Signal=FMC_NWE
PD6.GPIOParameters=GPIO_Speed,GPIO_Label
PD6.GPIO_Label=F2_MB
PD6.GPIO_Speed=GPIO_SPEED_FREQ_HIGH
PD6.Signal=S_TIM2_CH4
PD7.GPIOParameters=GPIO_Label
PD7.GPIO_Label=DISP_NE1_FMC
PD7.Mode=NorPsramChipSelect1_1
PD7.Signal=FMC_NE1
PD8.GPIOParameters=GPIO_Label
PD8.GPIO_Label=F1_ADC
PD8.Mode=IN12-Single-Ended
PD8.Signal=ADC5_IN12
PD9.GPIOParameters=GPIO_Label
PD9.GPIO_Label=F0_ADC
PD9.Mode=IN13-Single-Ended
PD9.Signal=ADC5_IN13
PE10.GPIOParameters=GPIO_Label
PE10.GPIO_Label=DISP_D7_FMC
PE10.Mode=8b-d1
PE10.Signal=FMC_D7
PE11.GPIOParameters=GPIO_Label
PE11.GPIO_Label=DISP_CS3
PE11.Signal=GPIO_Output
PE12.GPIOParameters=GPIO_Label
PE12.GPIO_Label=DISP_CS2
PE12.Signal=GPIO_Output
PE13.GPIOParameters=GPIO_Label
PE13.GPIO_Label=DISP_CS1
PE13.Signal=GPIO_Output
PE14.GPIOParameters=GPIO_Label
PE14.GPIO_Label=DISP_CS0
PE14.Signal=GPIO_Output
PE15.GPIOParameters=GPIO_Label
PE15.GPIO_Label=F0_TOUCH
PE15.Signal=GPIO_Input
PE4.GPIOParameters=GPIO_Speed,GPIO_Label
PE4.GPIO_Label=F3_MA
PE4.GPIO_Speed=GPIO_SPEED_FREQ_HIGH
PE4.Signal=S_TIM3_CH3
PE5.GPIOParameters=GPIO_Label
PE5.GPIO_Label=F3_TOUCH
PE5.Signal=GPIO_Input
PE6.GPIOParameters=GPIO_Label
PE6.GPIO_Label=F2_TOUCH
PE6.Signal=GPIO_Input
PE7.GPIOParameters=GPIO_Label
PE7.GPIO_Label=DISP_D4_FMC
PE7.Mode=8b-d1
PE7.Signal=FMC_D4
PE8.GPIOParameters=GPIO_Label
PE8.GPIO_Label=DISP_D5_FMC
PE8.Mode=8b-d1
PE8.Signal=FMC_D5
PE9.GPIOParameters=GPIO_Label
PE9.GPIO_Label=DISP_D6_FMC
PE9.Mode=8b-d1
PE9.Signal=FMC_D6
PF0-OSC_IN.GPIOParameters=GPIO_Label
PF0-OSC_IN.GPIO_Label=__OSC_IN
PF0-OSC_IN.Mode=HSE-External-Oscillator
PF0-OSC_IN.Signal=RCC_OSC_IN
PF1-OSC_OUT.GPIOParameters=GPIO_Label
PF1-OSC_OUT.GPIO_Label=__OSC_OUT
PF1-OSC_OUT.Mode=HSE-External-Oscillator
PF1-OSC_OUT.Signal=RCC_OSC_OUT
PF10.GPIOParameters=GPIO_Label
PF10.GPIO_Label=DISP_A0_FMC
PF10.Mode=A0_1
PF10.Signal=FMC_A0
PF2.GPIOParameters=GPIO_Label
PF2.GPIO_Label=LED_TEST
PF2.Signal=GPIO_Output
PF9.GPIOParameters=PinState,GPIO_Label
PF9.GPIO_Label=SHIFTREG_OE
PF9.PinState=GPIO_PIN_SET
PF9.Signal=GPIO_Output
RCC.HSE_VALUE=24000000
RCC.SYSCLKFreq_VALUE=170000000
RCC.SYSCLKSource=RCC_SYSCLKSOURCE_PLLCLK
board=custom

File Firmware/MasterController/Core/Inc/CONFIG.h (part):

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#define LOG_UART_HANDLE      huart2

/*=============================== SD CARD (mixes) ================================*/
/** The SD card on SPI3 (DISK_SCK PC10, DISK_MISO PC11, DISK_MOSI PC12, DISK_CS PA15): hardware_drivers/sd_spi.c,
 *  reached by FatFs through FATFS/Target/user_diskio.c. Mixes are .dgl files in its root (mix/mix_file.c). */
#define SD_SPI_HANDLE        hspi3

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
#define MCP23017_KNOBS_ADDR   0x20 // U7
#define MCP23017_PANEL_ADDR   0x21 // U8
#define MCP4728_ADDR          0x60 // U9 (factory address; LDAC is held low on PA10)

// ~390 kHz at PCLK1 = 170 MHz (PRESC 3, SCLDEL 11, SDADEL 2, SCLH 0x21, SCLL 0x3F). CubeMX has I2C2 at
// 100 kHz, too slow to read both expanders every millisecond, so i2c_init() applies this. Set I2C2
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/** Switching a return in or out of the mix first turns its level down, then back up, over this long each way */
static const uint32_t AUX_SWITCH_FADE_MS = 10;

/** LCV_INSERT (PE6) drives the insert relay on the analog board. Not set up in CubeMX yet: if it isn't,
 *  these stand in and control_outputs_init() makes it an output. */
#ifndef LCV_INSERT_Pin
#define LCV_INSERT_Pin       GPIO_PIN_6
#define LCV_INSERT_GPIO_Port GPIOE
#endif


/*=============================== LEDS ================================*/
/** As on the bucket: data out over SPI2 with DMA, latched on PB14 (LED_LAT), brightness a PWM on the knob
 *  boards' (active low) output enable from TIM1 channel 2 (PC1, LED_PWM). The two 74HCT595s for the
 *  button LEDs (U5, U6) have their output enable tied low, so brightness only dims the knob rings. */
#define LED_SPI_HANDLE         hspi2
#define LED_SPI_INSTANCE       SPI2
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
